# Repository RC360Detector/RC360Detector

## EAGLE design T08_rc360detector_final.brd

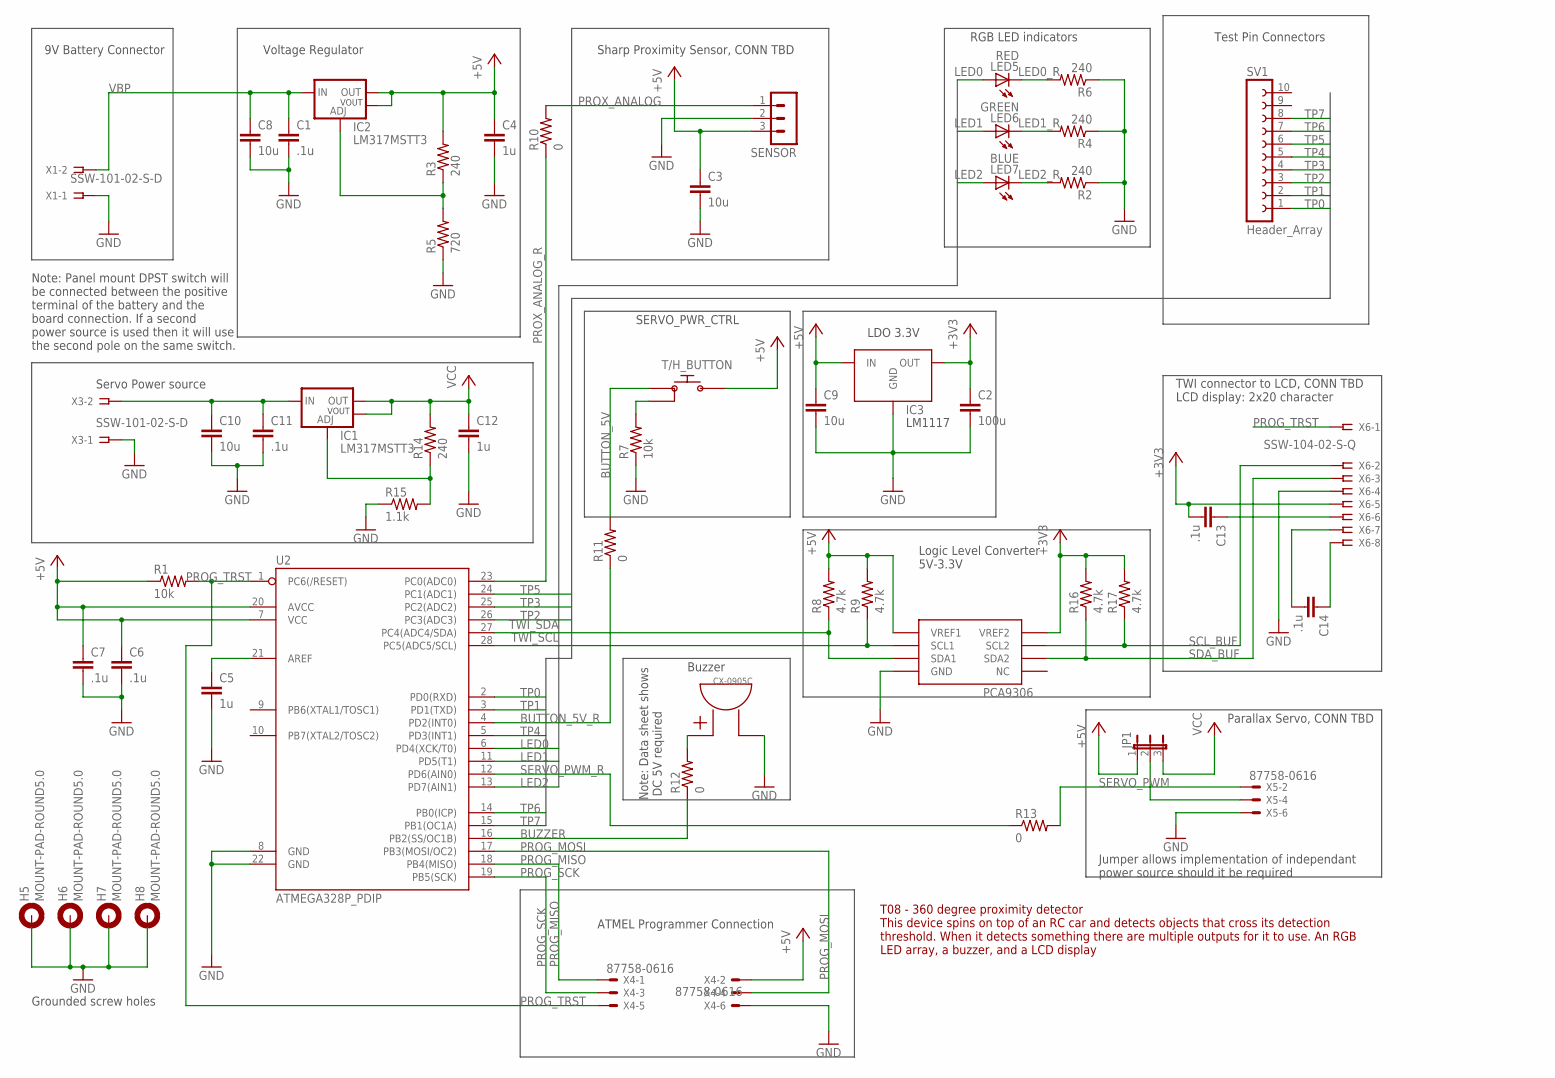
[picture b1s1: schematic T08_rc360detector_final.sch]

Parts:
C1, C6, C7, C11, C13, C14: .1u; C0805
C2: 100u; C0805
C3, C8, C9, C10: 10u; C0805
C4, C5, C12: 1u; C0805
CX-0905C: CX-0905C; BUZZER_CX-0905C
H5, H6, H7, H8: MOUNT-PAD-ROUND5.0; 5,0-PAD
IC1, IC2: LM317MSTT3; SOT223
IC3: LM1117; SOT-223
JP1: JP2E; JP2
LED5: RED; LD260
LED6: GREEN; LD260
LED7: BLUE; LD260
PCA9306: PCA9306_BREAKOUT
R1, R7: 10k; R0805
R2, R3, R4, R6, R14: 240; R0805
R5: 720; R0805
R8, R9, R16, R17: 4.7k; R0805
R10, R11, R12, R13: 0; R0805
R15: 1.1k; R0805
SENSOR: MA03-1
SV1: Header_Array; FE10
T/H_BUTTON: PR141C; 3_THROUGH_HOLE
U2: ATMEGA328P_PDIP; DIL28-3
X1, X3: SSW-101-02-S-D
X4, X5: 87758-0616
X6: SSW-104-02-S-Q

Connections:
+3V3: C2.1, C13.2, IC3.VOUT (OUT), PCA9306.VREF2, R16.2, R17.2, X6.5
+5V: C3.1, C4.1, C6.1, C7.1, C9.1, IC2.2 (VOUT), IC2.4 (OUT), IC3.IN, JP1.1, PCA9306.VREF1, R1.1, R3.2, R8.2, R9.2, SENSOR.3, T/H_BUTTON.P$3 (OUT), U2.7 (VCC), U2.20 (AVCC), X4.2
AREF: C5.1, U2.21 (AREF)
BUTTON_5V: R11.2, T/H_BUTTON.P$1 (IN)
BUTTON_5V_R: R11.1, U2.4 (PD2(INT0))
BUZZER: R12.1, U2.16 (PB2(SS/OC1B))
GND: C1.2, C2.2, C3.2, C4.2, C5.2, C6.2, C7.2, C8.2, C9.2, C10.2, C11.2, C12.2, CX-0905C.OUT, H5.B5, H6.B5, H7.B5, H8.B5, IC3.GND, PCA9306.GND, R2.1, R4.1, R5.1, R6.1, R7.1, R15.1, SENSOR.2, U2.8 (GND), U2.22 (GND), X1.1, X3.1, X4.6, X5.6, X6.4
LED0: LED5.A, U2.6 (PD4(XCK/T0))
LED0_R: LED5.K (C), R6.2
LED1: LED6.A, U2.11 (PD5(T1))
LED1_R: LED6.K (C), R4.2
LED2: LED7.A, U2.13 (PD7(AIN1))
LED2_R: LED7.K (C), R2.2
unnamed: R7.2, T/H_BUTTON.P$2 (GND)
unnamed: IC2.1 (ADJ), R3.1, R5.2
unnamed: CX-0905C.IN, R12.2
unnamed: IC1.1 (ADJ), R14.1, R15.2
unnamed: C10.1, C11.1, IC1.3 (IN), X3.2
unnamed: JP1.2, X5.4
unnamed: C13.1, X6.6
unnamed: C14.2, X6.7
unnamed: C14.1, X6.8
PROG_MISO: U2.18 (PB4(MISO)), X4.1
PROG_MOSI: U2.17 (PB3(MOSI/OC2)), X4.4
PROG_SCK: U2.19 (PB5(SCK)), X4.3
PROG_TRST: R1.2, U2.1 (PC6(/RESET)), X4.5, X6.1
PROX_ANALOG: R10.2, SENSOR.1
PROX_ANALOG_R: R10.1, U2.23 (PC0(ADC0))
SCL_BUF: PCA9306.SCL2, R17.1, X6.2
SDA_BUF: PCA9306.SDA2, R16.1, X6.3
SERVO_PWM: R13.2, X5.2
SERVO_PWM_R: R13.1, U2.12 (PD6(AIN0))
TP0: SV1.1, U2.2 (PD0(RXD))
TP1: SV1.2, U2.3 (PD1(TXD))
TP2: SV1.3, U2.26 (PC3(ADC3))
TP3: SV1.4, U2.25 (PC2(ADC2))
TP4: SV1.5, U2.5 (PD3(INT1))
TP5: SV1.6, U2.24 (PC1(ADC1))
TP6: SV1.7, U2.14 (PB0(ICP))
TP7: SV1.8, U2.15 (PB1(OC1A))
TWI_SCL: PCA9306.SCL1, R9.1, U2.28 (PC5(ADC5/SCL))
TWI_SDA: PCA9306.SDA1, R8.1, U2.27 (PC4(ADC4/SDA))
VBP: C1.1, C8.1, IC2.3 (IN), X1.2
VCC: C12.1, IC1.2 (VOUT), IC1.4 (OUT), JP1.3, R14.2

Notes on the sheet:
9V Battery Connector
Voltage Regulator
Sharp Proximity Sensor, CONN TBD
Parallax Servo, CONN TBD
ATMEL Programmer Connection
TWI connector to LCD, CONN TBD LCD display: 2x20 character
RGB LED indicators
Test Pin Connectors
SERVO_PWR_CTRL
Buzzer
T08 - 360 degree proximity detector This device spins on top of an RC car and detects objects that cross its detection threshold. When it detects something there are multiple outputs for it to use. An RGB LED array, a buzzer, and a LCD display
Note: Data sheet shows DC 5V required
Note: Panel mount DPST switch will be connected between the positive terminal of the battery and the board connection. If a second power source is used then it will use the second pole on the same switch.
Jumper allows implementation of independant power source should it be required
Servo Power source
LDO 3.3V
Logic Level Converter 5V-3.3V
Grounded screw holes

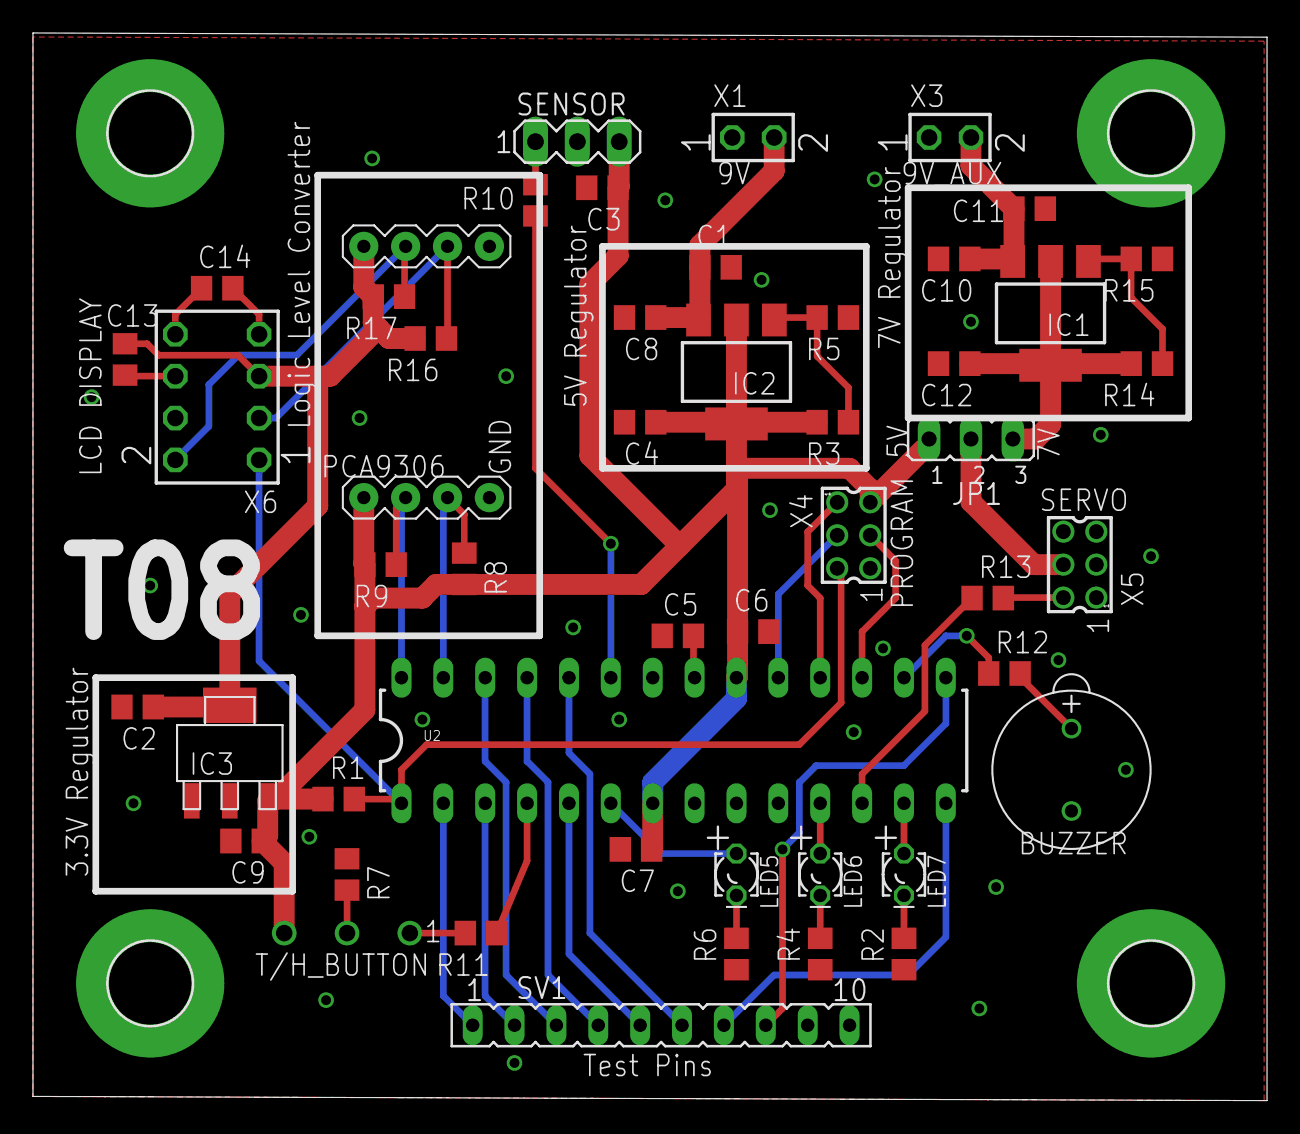
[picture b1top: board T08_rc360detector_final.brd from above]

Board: 2 copper layers, 74.9 x 64.8 mm, 53 parts (0 on the bottom side), 44 nets.

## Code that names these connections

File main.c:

/*
 * main.c
 *
 * GNU License:
 This program is free software: you can redistribute it and/or modify
 it under the terms of the GNU General Public License as published by
 the Free Software Foundation, either version 3 of the License, or
 (at your option) any later version.

 This program is distributed in the hope that it will be useful,
 but WITHOUT ANY WARRANTY; without even the implied warranty of
 MERCHANTABILITY or FITNESS FOR A PARTICULAR PURPOSE.  See the
 GNU General Public License for more details.

 You should have received a copy of the GNU General Public License
 along with this program.  If not, see <http://www.gnu.org/licenses/>.
 *
 */ 

#define F_CPU 8000000

#include <avr/io.h>
#include <stdint.h>
#include <util/delay.h>
#include <avr/interrupt.h>

/* Which analog pin we want to read from.  The pins are labeled "ADC0"
 * "ADC1" etc on the pin out in the data sheet.  In this case ADC_PIN
 * being 0 means we want to use ADC0.  On the ATmega328P this is also
 * the same as pin PC0 */
 
#define ADC_PIN			0
#define ADC_NEAR		125
#define ADC_FAR			55
#define	LED_PIN			PB0
#define	BUZZ			PB2
#define LED0			PD5			
#define LED1			PD4
#define LED2			PD7
#define	INT_LED			PB1


/* This function just keeps the reading code out of the loop itself.
 * It takes the analog pin number as a parameter and returns the
 * analog reading on that pin as a result.
 *
 * Look for its definition below main. */
 
//Function Declarations 
uint16_t adc_read(uint8_t adcx);
void ioinit(void);      //Initializes IO
void delay_ms(uint16_t x); //General purpose delay
void Wait(){
	uint16_t i;
	for(i=0;i<50;i++)
	{
		_delay_loop_2(0);
		_delay_loop_2(0);
		_delay_loop_2(0);
	}
}

int main(void){
	
	DDRD &= ~(1 << DDD2);     // Clear the PD2 pin
	// PD2 (PCINT0 pin) is now an input - input from button
		
	EICRA &= ~(1 << ISC01);    // set INT0 to trigger on any state change
	EICRA |= (1 << ISC00);
	
	EIMSK |= (1 << INT0);     // Turns on INT0

	DDRD |= (1 << DDD6) | //servo
			(1 << DDD7) | //red LED			
			(1 << DDD5) | //blue LED
			(1 << DDD4);  //green LED

	DDRB |= (1 << DDB2) | //buzzer
			(1 << DDB1);  //debug LED
	

	OCR0A = 128;
	// set PWM for 50% duty cycle

	TCCR0A |= (1 << WGM01) | (1 << WGM00);
	// set fast PWM Mode

	ioinit();			
	sei();                    // turn on interrupts
	PORTB |= _BV(LED2);
	PORTB |= _BV(LED1);
	PORTB |= _BV(LED0);
		
	//intialize pwm to off
	TCCR0A &= ~(1 << COM0A1);// set none-inverting mode
	TCCR0B &= ~(1 << CS02);
	for (;;){
		if(adc_read(ADC_PIN) > ADC_NEAR) //close distance object
		{
			PORTD |= _BV(LED0);			//turn red LED on
			PORTD &= ~_BV(LED1);		//confirms other two LEDs are off
			PORTD &= ~_BV(LED2);
			PORTB |= _BV(BUZZ);			//turns buzzer on
		}
		else if ((adc_read(ADC_PIN) < ADC_NEAR) && (adc_read(ADC_PIN) > ADC_FAR)) //medium distance object
		{
			PORTD &= ~_BV(LED0);		//turn off other 2 LEDs and buzzer
			PORTD |= _BV(LED1);			//turns on blue LED
			PORTD &= ~_BV(LED2);
			PORTB &= ~_BV(BUZZ);
		}
		else if ((adc_read(ADC_PIN) < ADC_FAR)) //no object in sight
		{
			PORTD &= ~_BV(LED0);
			PORTD &= ~_BV(LED1);
			PORTD |= _BV(LED2);		//turn on green LED
			PORTB &= ~_BV(BUZZ);	//turn off other two LEDs and buzzer
		}

	}

}

void ioinit (void)
{

	DDRB  |= _BV(LED_PIN);
	
	ADMUX |= (1<<REFS0);
	//set prescaller to 128 and enable ADC
	ADCSRA |= (1<<ADPS2)|(1<<ADPS1)|(1<<ADPS0)|(1<<ADEN);
}

uint16_t adc_read(uint8_t adcx) {
	/* adcx is the analog pin we want to use.  ADMUX's first few bits are
	 * the binary representations of the numbers of the pins so we can
	 * just 'OR' the pin's number with ADMUX to select that pin.
	 * We first zero the four bits by setting ADMUX equal to its higher
	 * four bits. */
	ADMUX	&=	0xf0;
	ADMUX	|=	adcx;

	/* This starts the conversion. */
	ADCSRA |= _BV(ADSC);

	/* This is an idle loop that just wait around until the conversion
	 * is finished.  It constantly checks ADCSRA's ADSC bit, which we just
	 * set above, to see if it is still set.  This bit is automatically
	 * reset (zeroed) when the conversion is ready so if we do this in
	 * a loop the loop will just go until the conversion is ready. */
	while ( (ADCSRA & _BV(ADSC)) );

	/* Finally, we return the converted value to the calling function. */
	return ADC;
}

//interrupt service routine
//checks voltage level on pin PD2
//if voltage is high it turns on PWM and a debug LED which is non populated on board
ISR (INT0_vect)
{
	//PORTB ^= _BV(LED);
	//checks value on PD2 and if high sets the PWM prescaleer and turns on PWM
	//motor will begin to spin
	if (PIND & (1<<PD2)){		
		TCCR0A |= (1 << COM0A1);// set none-inverting mode
		TCCR0B |= (1 << CS01);	//500 Hz PWM
		PORTB |= _BV(INT_LED);
	
	//when voltage on PD2 is low, the PWM will be turn off
	//motor will stop spinning and LED will turn off
	} else {
		// set none-inverting mode
		TCCR0A &= ~(1 << COM0A1);// set none-inverting mode
		TCCR0B &= ~(1 << CS01);
		PORTB &= ~_BV(INT_LED);
		
	}
	
	_delay_ms(250); //debounce loop for safety
}

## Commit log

2015-10-20 Adding empty version of main.c for the atmega 328p.
2015-10-24 Adding requirements document
2015-10-24 Adding class requirements
2015-10-25 Adding c program for blinking LED to the repo.
2015-10-26 Adding pdf of spec sheet for the wiki.
2015-10-28 Schematic
    -Added frame and info boxes
    -changed layer of text to 'info'
    -changed symbols of resistors and caps to American and European,
    respectively
    -combined caps that where in parallel
2015-10-30 Update
    -Added RGB LEDs
    -Reorganized layout
    -Added TWI (aka I2C) interface connections
    -Added Test points to critical signals
2015-10-31 Code works with proximity sensor.
2015-10-31 Got motor working
2015-11-01 Dif file
    Added bus to LED lines
    Added Test Points to unused uC pins
    Added Buzzer circuit
    Added Button circuit
    Added switch between battery and volt reg
    Moved reset jumper
2015-11-02 New file that contains proper file name
    changed power caps
    aqdded vcc caps
    added pull ups on TWI lines
    changed aref cap value
    labeled micro controller
    removed jumpers
2015-11-03 First pass at board layout
    Started board layout. The problems:
    -The current atmega328 block is way too small for us to solder, changed
    to the pdip for the moment
    -not sure if I got the rules check file working
    -PCB layers are at 16, and it should be 2
    -Need mounting screws tied to ground added to sch
2015-11-04 2nd pass
    -Added custom library that contains button and buzzer
    -Routed rest of connections. Left TWI interface out until Jared adds the
    finished connections to the schematic
    -Added screw holes, can resize if we want bigger screws
    -Added some basic silk screen
    -Added jumper for servo so we can switch it between if needed.
2015-11-04 Adding Naser's project files.
2015-11-05 Added LM1117
    Added LDO voltage regulator LM1117 w/ SOT-223 layout
2015-11-06 Update
    Rerouted layout with new TWI circuitry. The logic converter IC is so
    small the chip doesnt pass DRC, so I informed Jared and he's looking
    into an alternate solution. Also the current chip is PDIP but I'm
    debating changing it to TQFP. Will need to discuss tomorrow.
2015-11-07 Added interrupt code.
2015-11-07 Got pwm enable working on interrupt.
2015-11-07 Adding 3 LED code, in progress.
2015-11-09 Finished preliminary layout
    Finished layout after feedback today
    Also made an alternate layout that I feel is cleaner and experimented
    with importing silkscreen images.
2015-11-09 Slight changes. Passed DRC
    Made sure DRC worked and had updated libraries. This should work now,
    (hopefully)
2015-11-11 Supposedly last submission of board
    -Changed LM1117 caps to higher values as per datasheet
    -compacted layout to take up less space
    -Changed to larger diameter mounting holes
    -Connected floating vout pin on lm317s to other vout
    -Changed jumper to format that uses header pins
2015-11-14 Adding in Jared's 3-LED code.
2015-11-18 Adding system modeling stuff.
2015-11-18 Adding level 1 diagram.
2015-11-18 Adding level zero block dgrm.
2015-11-18 Removing LCD from level zero.
2015-11-18 Adding state diagram.
2015-11-18 Adding sensor subsystem.
2015-11-18 Adding level 0 subsystems.
2015-11-18 Adding physical view.
2015-11-23 Adding test plan documents.
2015-11-23 Fixed typo on motor testplan.
2015-12-05 Presentation Power Point
    First pass at relevant topics
2015-12-10 Fixing up test plans
2015-12-10 More work on test plans.
2015-12-10 BOM for 360 detector project
2015-12-10 Removing some renamed files.
2015-12-10 adding revised motor test plan
2015-12-10 Adding licence and final version of code.
2015-12-10 Updating requirements doc.
2015-12-10 Fixing malformatted line in requirements doc.
2015-12-10 Adding revised state diagram.
2015-12-10 Updating presentation.
2015-12-10 Updating presentation and task view.
2015-12-10 Removing some outdated stuff from main.c, updating project schedule.
2015-12-10 One more fix to ppt.
2015-12-11 Adding pdf of presentation.

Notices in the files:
parts and their libraries:
SparkFun-DigitalIC: Licensing: Creative Commons ShareAlike 4.0 International - https://creativecommons.org/licenses/by-sa/4.0
